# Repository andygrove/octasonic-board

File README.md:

# Octasonic 8 x HC-SR04 Breakout Board

For full documentation, please see: https://theotherandygrove.com/octasonic/

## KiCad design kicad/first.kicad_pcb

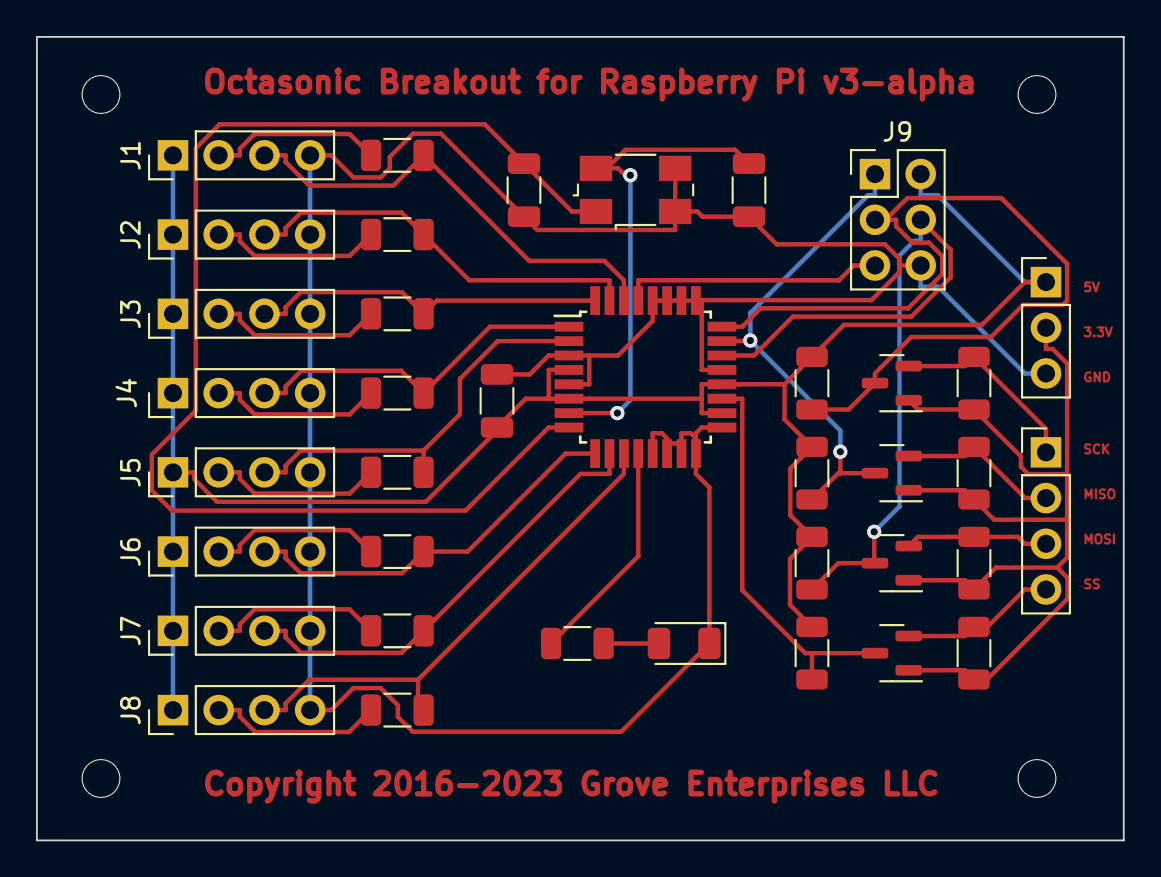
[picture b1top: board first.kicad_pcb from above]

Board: 2 copper layers, 60.4 x 44.6 mm, 42 parts (0 on the bottom side), 32 nets.

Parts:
C1, C2: 22pF; C_1206_3216Metric
C3: 0.1uF; C_1206_3216Metric
D1: LED; LED_1206_3216Metric
J1, J2, J3, J4, J5, J6, J7, J8, J11: Conn_01x04_Pin; PinHeader_1x04_P2.54mm_Vertical
J9: AVR-ISP-6; PinHeader_2x03_P2.54mm_Vertical
J10: Conn_01x03_Pin; PinHeader_1x03_P2.54mm_Vertical
Q1, Q2, Q3, Q4: BSS138; SOT-23
R1, R2, R3, R4, R5, R6, R7, R8: 2.2k; R_1206_3216Metric
R9, R10, R12, R13, R14, R15, R16, R17: 10k; R_1206_3216Metric
R11: 330; R_1206_3216Metric
U1: ATmega328-A; TQFP-32_7x7mm_P0.8mm
Y1: Crystal_GND23; Crystal_SMD_0603-4Pin_6.0x3.5mm
drill1, drill2, drill3, drill4: MountingHole_2.1mm

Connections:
+3.3V: J10.2, Q1.1 (G), Q2.1 (G), Q3.1 (G), Q4.1 (G), R9.2, R12.2, R14.2, R16.2
+5V: C3.1, J1.1, J2.1, J3.1, J4.1, J5.1, J6.1, J7.1, J8.1, J9.2 (VCC), J10.1, R10.2, R13.2, R15.2, R17.2, U1.4 (VCC), U1.6 (VCC), U1.18 (AVCC), U1.20 (AREF)
/MISO_HV: J9.1 (MISO), Q2.3 (D), R13.1, U1.23 (PC0)
/MISO_LV: J11.2, Q2.2 (S), R12.1
/MOSI_HV: J9.4 (MOSI), Q1.3 (D), R10.1, U1.22 (ADC7)
/MOSI_LV: J11.3, Q1.2 (S), R9.1
/PD0: J1.3, R1.2, U1.30 (PD0)
/PD1: J2.3, R2.2, U1.31 (PD1)
/PD2: J3.3, R3.2, U1.32 (PD2)
/PD3: J4.3, R4.2, U1.1 (PD3)
/PD4: J5.3, R5.2, U1.2 (PD4)
/PD5: J6.3, R6.2, U1.9 (PD5)
/PD6: J7.3, R7.2, U1.10 (PD6)
/PD7: J8.3, R8.2, U1.11 (PD7)
/RESET: J9.5 (~RST), U1.29 (~RESET/PC6)
/SCK_HV: J9.3 (SCK), Q3.3 (D), R15.1, U1.24 (PC1)
/SCK_LV: J11.1, Q3.2 (S), R14.1
/SS_HV: Q4.3 (D), R17.1, U1.19 (ADC6)
/SS_LV: J11.4, Q4.2 (S), R16.1
GND: C1.2, C2.2, C3.2, D1.1 (K), J1.4, J2.4, J3.4, J4.4, J5.4, J6.4, J7.4, J8.4, J9.6 (GND), J10.3, U1.3 (GND), U1.5 (GND), U1.13 (PB1), U1.14 (PB2), U1.15 (PB3), U1.16 (PB4), U1.17 (PB5), U1.21 (GND), U1.25 (PC2), U1.26 (PC3), U1.27 (PC4), U1.28 (PC5), Y1.2, Y1.3
unnamed: D1.2 (A), R11.1
unnamed: J1.2, R1.1
unnamed: J2.2, R2.1
unnamed: J3.2, R3.1
unnamed: J4.2, R4.1
unnamed: J5.2, R5.1
unnamed: J6.2, R6.1
unnamed: J7.2, R7.1
unnamed: J8.2, R8.1
unnamed: R11.2, U1.12 (PB0)
unnamed: C2.1, U1.7 (XTAL1/PB6), Y1.4
unnamed: C1.1, U1.8 (XTAL2/PB7), Y1.1

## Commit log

2015-12-13 set up project structure
2015-12-13 rough out master/slave
2015-12-13 save
2015-12-13 rename folders
2015-12-13 SPI working between Arduino master and AVR slave
2015-12-13 change fuse bits for 16 MHz
2015-12-13 remove avr-master
2015-12-15 implements get/set sensor count protocol
2015-12-15 slave with interrupts is working, but clock divider is wrong (counting 16x too fast)
2015-12-16 reading sensor and reporting results
2015-12-16 single pin for sensor
2015-12-16 can now read 6 sensors
2015-12-16 can now read 8 sensors on port D
2015-12-16 initial board layout
2016-01-10 improve board layout
2016-01-24 fixed missing SS connection in schematic, also switched to 5mm capacitor and completely redesigned board layout
2016-01-24 refining board layout
2016-01-24 add v1 of smd layout .. is missing SS connection
2016-01-24 changed first connecter to swap trig/echo
2016-01-24 finished swapping trig/echo on all connectors
2016-02-06 Fix error on board (AVR ISP did not have SCK routed)
2016-03-04 change branding on board
2016-09-03 sleep 50 ms between readings, time out at 200 cm
2017-05-10 update board to use locking molex connectors
2018-01-18 remove everything except board design (code has moved to other repos)
2023-11-03 add kicad board
2023-11-04 latest
2023-11-04 rename

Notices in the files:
kicad/first.kicad_pcb:
Copyright 2016-2023 Grove Enterprises LLC
